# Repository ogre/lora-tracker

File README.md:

# SUSF LoRa HAB Tracker System 

Phil currently uses the following combination:

### *slim-board/* - Eagle layout of a slimline HAB Tracker PCB

* AAA Energizer Ultimate L92 Lithium power source
* ADP1607 DC-DC Boost Regulator
* STM32F030 Microcontroller
* u-blox MAX-M8x GNSS Receiver
* RFM98W 434MHz LoRa Transceiver Module

### *firmware-tracker-phil/* - Firmware for LoRa/RTTY HAB Trackers

* libopencm3-based firmware
* payload-switched config system
* u-blox GNSS aid data storage

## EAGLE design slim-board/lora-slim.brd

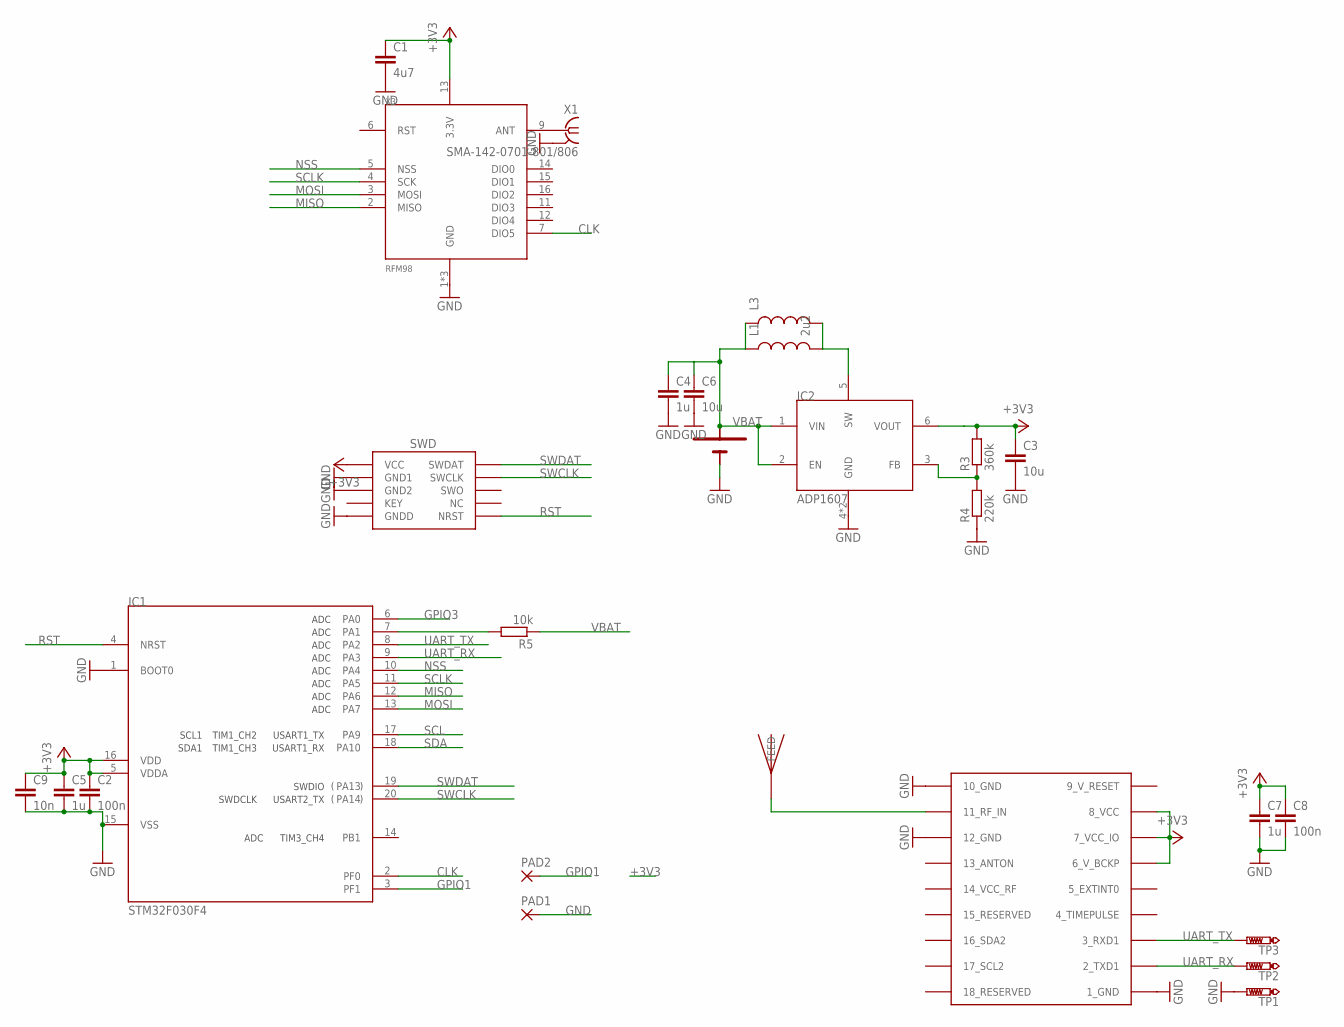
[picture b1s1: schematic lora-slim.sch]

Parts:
C1: 4u7; C0603
C2, C8: 100n; C0603
C3, C6: 10u; C0805
C4, C5, C7: 1u; C0603
C9: 10n; C0603
IC1: STM32F030F4; TSSOP20
IC2: ADP1607; LFCSP6
J1: SWD_PTH_SHROUD
L1: 2u2; 0805
L3: INDUCTOR1210; 1210
PAD1, PAD2: 2,15/1,0
R3: 360k; R0603
R4: 220k; R0603
R5: 10k; R0603
TP1, TP2, TP3: PTR1B1,27; B1,27
U$5: JTI_ANTENNA-1575AT43A40
U$6: KEYSTONE-53; KEYSTONE53
X1: SMA-142-0701-801/806; J502-ND-142-0701-801/806
X2: UBLOX_MAX
X3: RFM98; RFM97

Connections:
9_V_RESET: X2.9_V_RESET
+3V3: C1.1, C2.1, C3.1, C5.1, C7.1, C8.1, C9.1, IC1.5 (VDDA), IC1.16 (VDD), IC2.6 (VOUT), J1.1 (VCC), R3.2, X2.6_V_BCKP, X2.7_VCC_IO, X2.8_VCC, X3.13 (3.3V)
CLK: IC1.2 (PF0), X3.7 (DIO5)
GND: C1.2, C2.2, C3.2, C4.2, C5.2, C6.2, C7.2, C8.2, C9.2, IC1.1 (BOOT0), IC1.15 (VSS), IC2.4 (GND), IC2.EP (GND), J1.3 (GND1), J1.5 (GND2), J1.9 (GNDD), PAD1.1, R4.1, TP1.TP, U$6.N1 (-), U$6.N2 (-), X1.G@1 (2), X1.G@2 (2), X1.G@3 (2), X1.G@4 (2), X2.1_GND, X2.10_GND, X2.12_GND, X3.1 (GND), X3.8 (GND), X3.10 (GND)
GPIO1: IC1.3 (PF1), PAD2.1
GPIO3: IC1.6 (PA0)
MISO: IC1.12 (PA6), X3.2 (MISO)
MOSI: IC1.13 (PA7), X3.3 (MOSI)
unnamed: U$5.FEED, X2.11_RF_IN
unnamed: X1.1, X3.9 (ANT)
unnamed: IC2.5 (SW), L1.2, L3.2
unnamed: IC2.3 (FB), R3.1, R4.2
unnamed: IC1.7 (PA1), R5.2
NSS: IC1.10 (PA4), X3.5 (NSS)
RST: IC1.4 (NRST), J1.10 (NRST)
SCL: IC1.17 (PA9)
SCLK: IC1.11 (PA5), X3.4 (SCK)
SDA: IC1.18 (PA10)
SWCLK: IC1.20 (PA14), J1.4 (SWCLK)
SWDAT: IC1.19 (PA13), J1.2 (SWDAT)
UART_RX: IC1.9 (PA3), TP2.TP, X2.2_TXD1
UART_TX: IC1.8 (PA2), TP3.TP, X2.3_RXD1
VBAT: C4.1, C6.1, IC2.1 (VIN), IC2.2 (EN), L1.1, L3.1, R5.1, U$6.P1 (+), U$6.P2 (+)

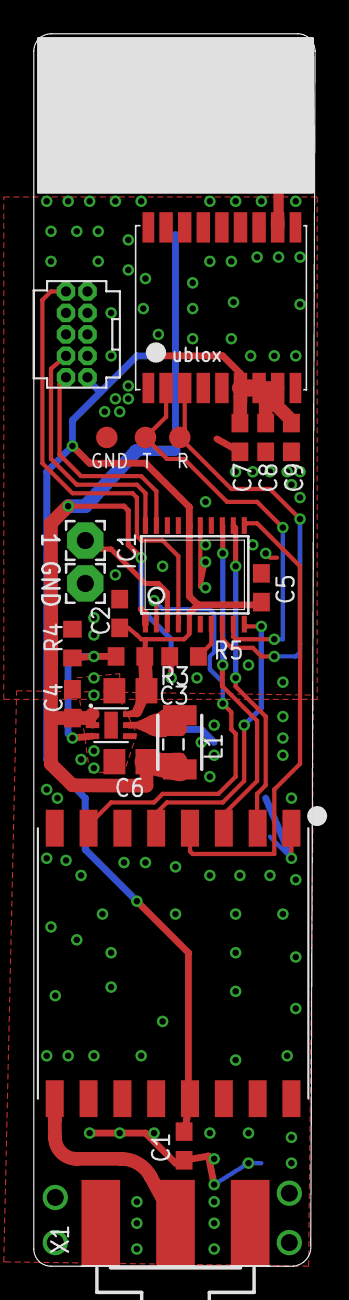
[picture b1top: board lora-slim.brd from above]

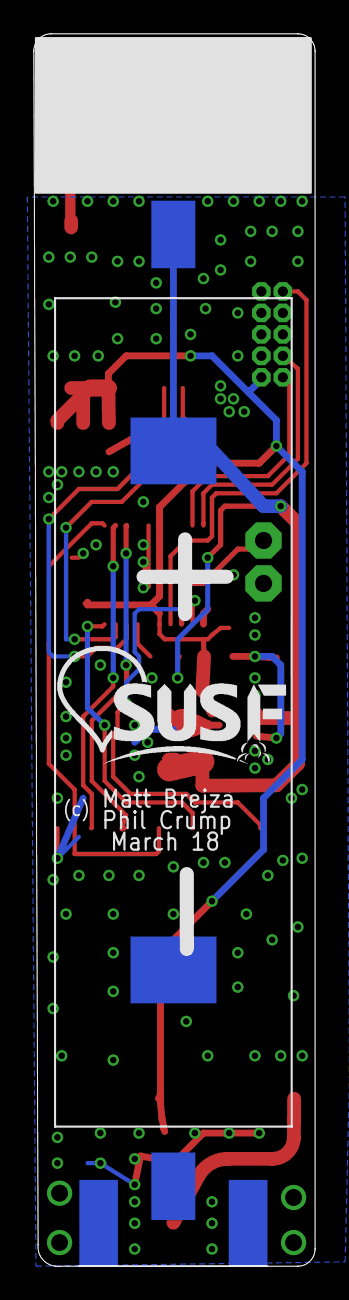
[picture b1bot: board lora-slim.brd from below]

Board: 2 copper layers, 16.6 x 72.9 mm, 28 parts (2 on the bottom side), 19 nets.

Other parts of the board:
U$1: SUSF-XSM

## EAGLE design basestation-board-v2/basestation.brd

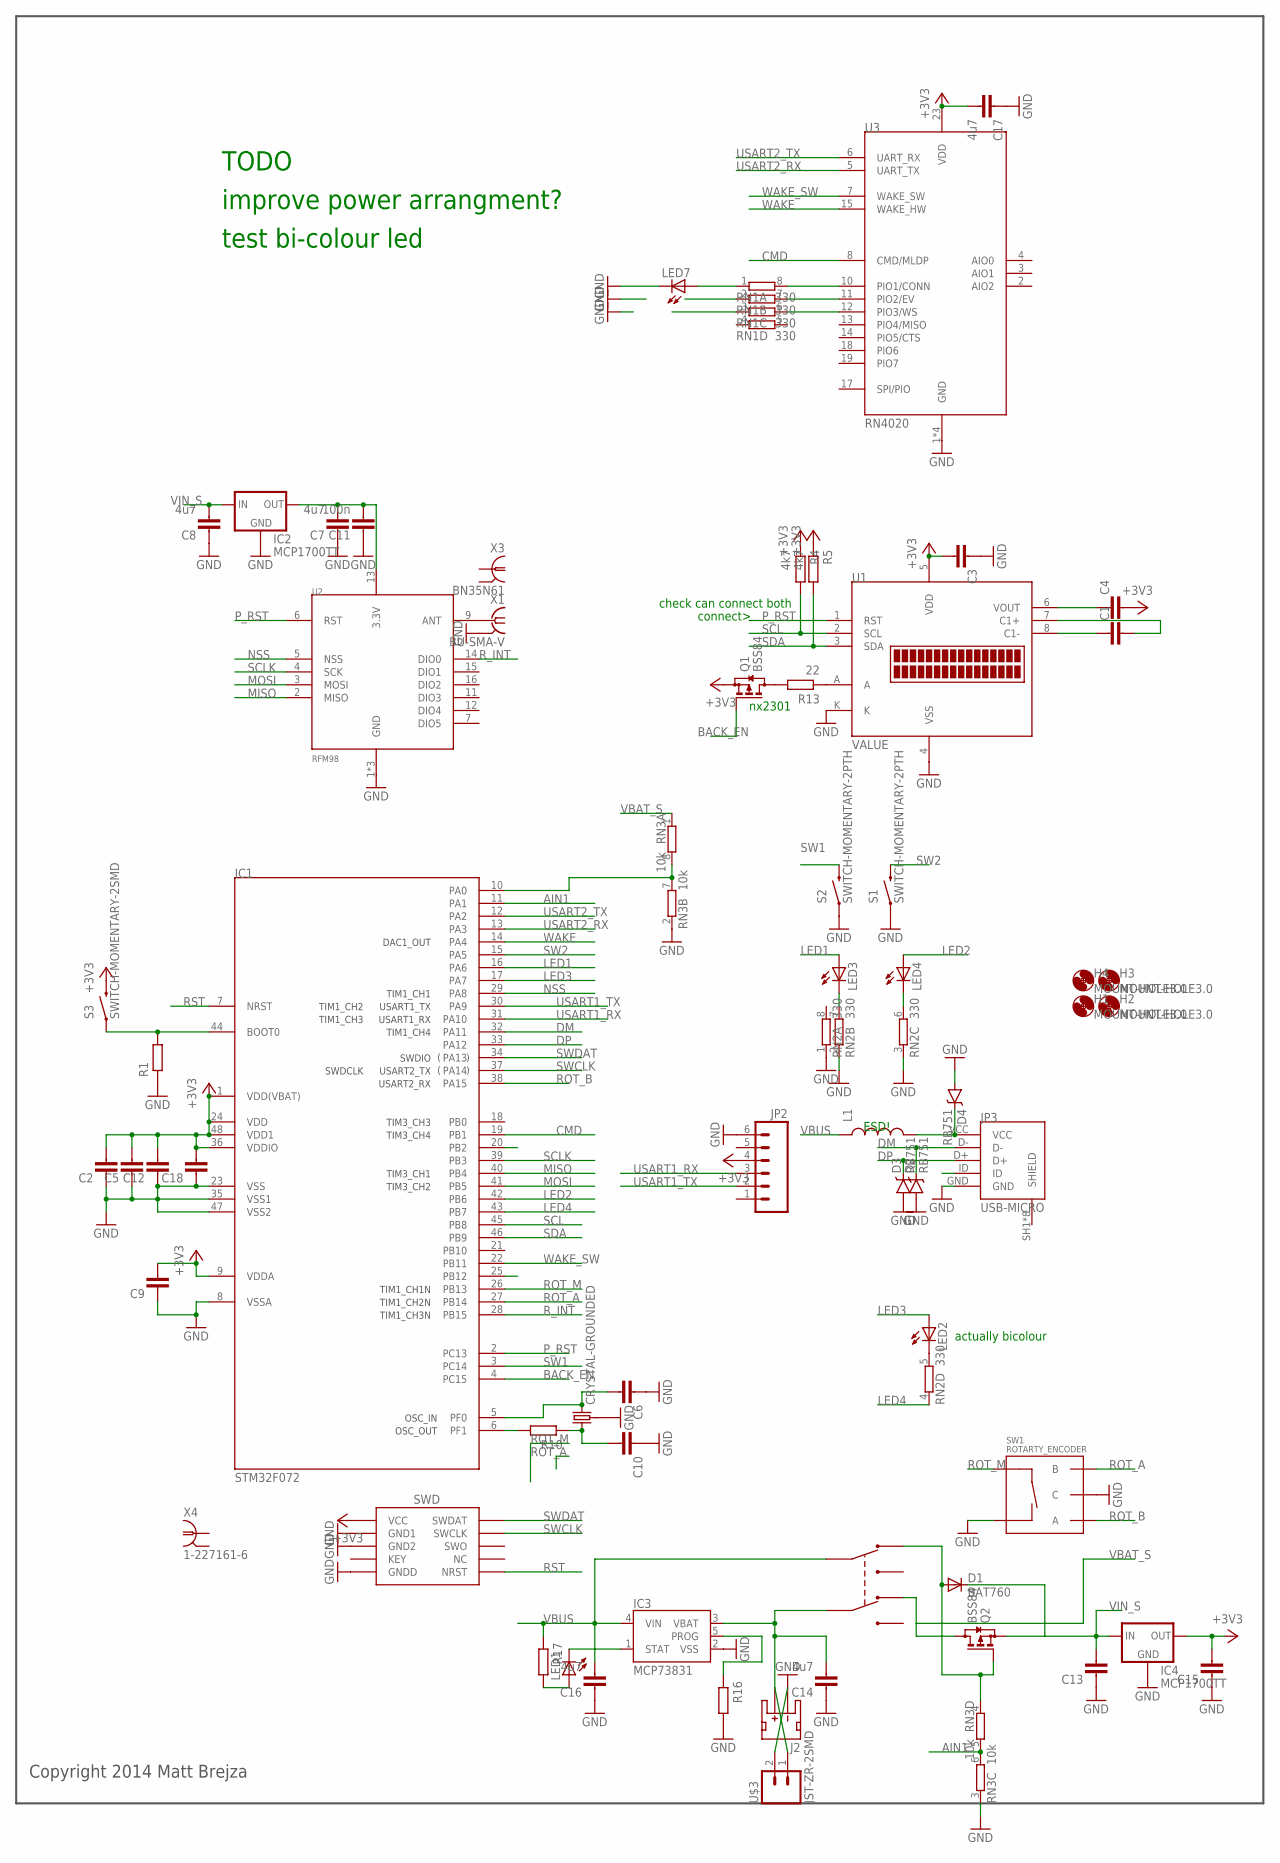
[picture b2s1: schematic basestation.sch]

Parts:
C1, C2, C3, C4, C5, C6, C9, C10, C12, C13, C15, C18: CAPACITOR0603-N; C0603-N
C7, C8, C14, C16, C17: 4u7; C0603-N
C11: 100n; C0603-N
D1: BAT760; SOD323-R
D2, D3, D4: RB751; SOD-523
H1, H2, H3, H4: MOUNT-HOLE3.0; 3,0
IC1: STM32F072; TQFP48
IC2, IC4: MCP1700TT; SOT23
IC3: MCP73831; SOT23-5
J1: SWD_SHROUD_SMD; SWD_SMD_SHROUD
J2: JST_2MM_MALE; JST-2-SMD
JP2: M06SMD; 1X06-SMD
JP3: USB-MICRO; MOLEX_47589-0001
L1: INDUCTOR0603; 0603
LED1, LED7: LEDCHIP-LED0805; CHIP-LED0805
LED2: LED5MM
LED3, LED4: LED3MM
Q1, Q2: BSS84; SOT23
R1, R10, R16, R17: RESISTOR0603-N; R0603-N
R4, R5: 4k7; R0603-N
R13: 22; R0603-N
RN1, RN2: 330; EXB38V
RN3: 10k; EXB38V
S1, S2: SWITCH-MOMENTARY-2PTH; TACTILE-PTH
S3: SWITCH-MOMENTARY-2SMD; TACTILE_SWITCH_SMD
SW1: ROTARTY_ENCODER; ROTARY_ENC_PLAIN
U1: NHD-C0216CIZ-FSW
U2: RFM98; RFM97
U3: RN4020
U$1: DPDTSLIDE
U$3: JST-ZR-2SMD; JST-ZR-2-SMD
X1: BU-SMA-V
X2: CRYSTAL-GROUNDED; CRYSTAL-SMD-5X3
X3: BN35N61; B35N61
X4: 1-227161-6; AMP_227161

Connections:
3.3V: C7.2, C11.2, IC2.2 (OUT), U2.13 (3.3V)
+3V3: C2.2, C3.2, C4.2, C5.2, C9.2, C12.2, C15.2, C17.2, C18.2, IC1.1 (VDD(VBAT)), IC1.9 (VDDA), IC1.24 (VDD), IC1.36 (VDDIO), IC1.48 (VDD1), IC4.2 (OUT), J1.1 (VCC), JP2.4, Q1.2 (S), R4.1, R5.1, S3.3 (2), U1.5 (VDD), U3.23 (VDD)
AIN1: IC1.11 (PA1), RN3.5 (2), RN3.6 (2)
BACK_EN: IC1.4 (PC15), Q1.1 (G)
CMD: IC1.19 (PB1), U3.8 (CMD/MLDP)
DM: D2.C, IC1.32 (PA11), JP3.D-
DP: D3.C, IC1.33 (PA12), JP3.D+
GND: C2.1, C3.1, C5.1, C6.1, C7.1, C8.1, C9.1, C10.1, C11.1, C12.1, C13.1, C14.1, C15.1, C16.1, C17.1, C18.1, D2.A, D3.A, D4.A, IC1.8 (VSSA), IC1.23 (VSS), IC1.35 (VSS1), IC1.47 (VSS2), IC2.1 (GND), IC3.2 (VSS), IC4.1 (GND), J1.3 (GND1), J1.5 (GND2), J1.9 (GNDD), J2.1 (-), JP2.6, JP3.GND, LED7.C, R1.1, R16.2, RN2.1, RN2.2 (1), RN2.3 (1), RN3.2 (1), RN3.3 (1), S1.1, S2.1, SW1.C, SW1.SW-, U1.4 (VSS), U1.K, U2.1 (GND), U2.8 (GND), U2.10 (GND), U3.1 (GND), U3.9 (GND), U3.16 (GND), U3.24 (GND), U$3.2, X1.2, X1.3 (2), X1.4 (2), X1.5 (2), X2.2 (3), X2.4 (3)
LED1: IC1.16 (PA6), LED3.A
LED2: IC1.42 (PB6), LED4.A
LED3: IC1.17 (PA7), LED2.A
LED4: IC1.43 (PB7), RN2.4 (1)
MISO: IC1.40 (PB4), U2.2 (MISO)
MOSI: IC1.41 (PB5), U2.3 (MOSI)
unnamed: U2.9 (ANT), X1.1
unnamed: Q1.3 (D), R13.2
unnamed: IC1.44 (BOOT0), R1.2, S3.1
unnamed: RN1.8 (2), U3.10 (PIO1/CONN)
unnamed: LED3.K (C), RN2.7 (2)
unnamed: IC3.5 (PROG), R16.1
unnamed: C1.1, U1.8 (C1-)
unnamed: C1.2, U1.7 (C1+)
unnamed: LED4.K (C), RN2.6 (2)
unnamed: LED2.K (C), RN2.5 (2)
unnamed: C4.1, U1.6 (VOUT)
unnamed: RN1.7 (2), U3.11 (PIO2/EV)
unnamed: RN1.6 (2), U3.12 (PIO3/WS)
unnamed: LED7.A, RN1.1
unnamed: R13.1, U1.A
unnamed: D1.A, Q2.1 (G), RN3.4 (1), U$1.1A (NC0)
unnamed: IC1.10 (PA0), RN3.7 (2), RN3.8 (2)
unnamed: IC3.1 (STAT), LED1.C
unnamed: IC1.6 (PF1), R10.2
unnamed: C6.2, IC1.5 (PF0), X2.1 (2)
unnamed: C10.2, R10.1, X2.3 (1)
unnamed: C14.2, IC3.3 (VBAT), J2.2 (+), U$1.2X (COM1), U$3.1
unnamed: LED1.A, R17.2
unnamed: D4.C, JP3.VCC, L1.2
NSS: IC1.29 (PA8), U2.5 (NSS)
P_RST: IC1.2 (PC13), U1.1 (RST), U2.6 (RST)
ROT_A: IC1.27 (PB14), SW1.B
ROT_B: IC1.38 (PA15), SW1.A
ROT_M: IC1.26 (PB13), SW1.SW+
RST: IC1.7 (NRST), J1.10 (NRST)
R_INT: IC1.28 (PB15), U2.14 (DIO0)
SCL: IC1.45 (PB8), R4.2, U1.2 (SCL)
SCLK: IC1.39 (PB3), U2.4 (SCK)
SDA: IC1.46 (PB9), R5.2, U1.3 (SDA)
SW1: IC1.3 (PC14), S2.3 (2)
SW2: IC1.15 (PA5), S1.3 (2)
SWCLK: IC1.37 (PA14), J1.4 (SWCLK)
SWDAT: IC1.34 (PA13), J1.2 (SWDAT)
USART1_RX: IC1.31 (PA10), JP2.3
USART1_TX: IC1.30 (PA9), JP2.2
USART2_RX: IC1.13 (PA3), U3.5 (UART_TX)
USART2_TX: IC1.12 (PA2), U3.6 (UART_RX)
VBAT_S: Q2.3 (D), RN3.1, U$1.2A (NC1)
VBUS: C16.2, IC3.4 (VIN), L1.1, R17.1, U$1.1X (COM0)
VIN_S: C8.2, C13.2, D1.C, IC2.3 (IN), IC4.3 (IN), Q2.2 (S)
WAKE: IC1.14 (PA4), U3.15 (WAKE_HW)
WAKE_SW: IC1.22 (PB11), U3.7 (WAKE_SW)

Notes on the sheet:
actually bicolour
connect>
nx2301
ESD!
check can connect both
Copyright 2014 Matt Brejza
TODO
improve power arrangment?
test bi-colour led

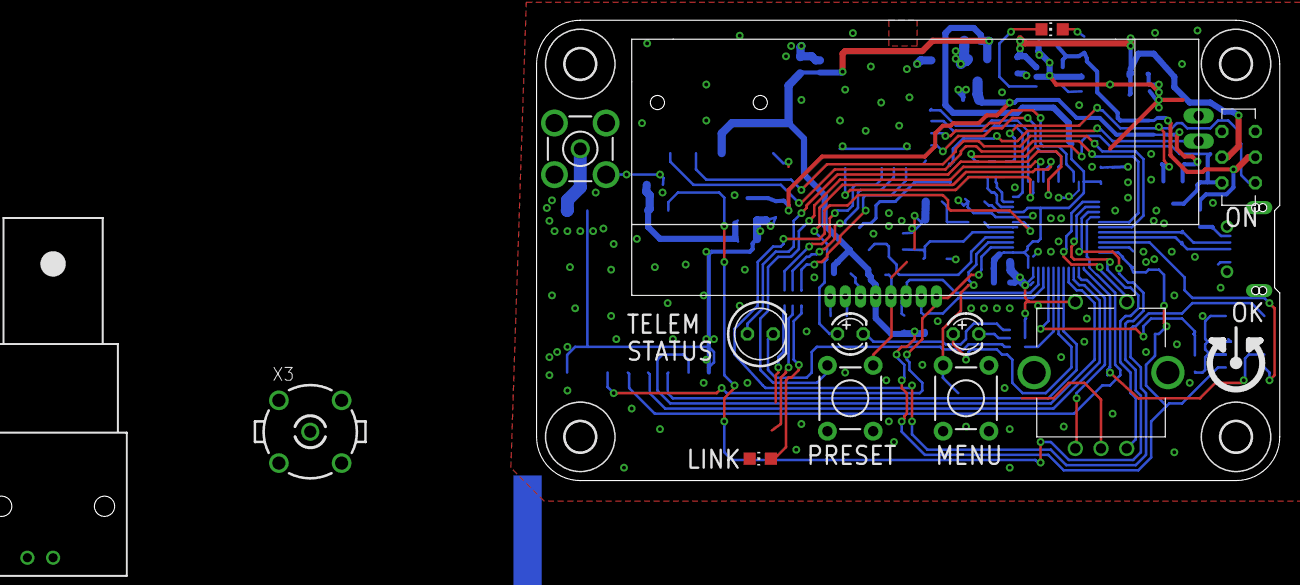
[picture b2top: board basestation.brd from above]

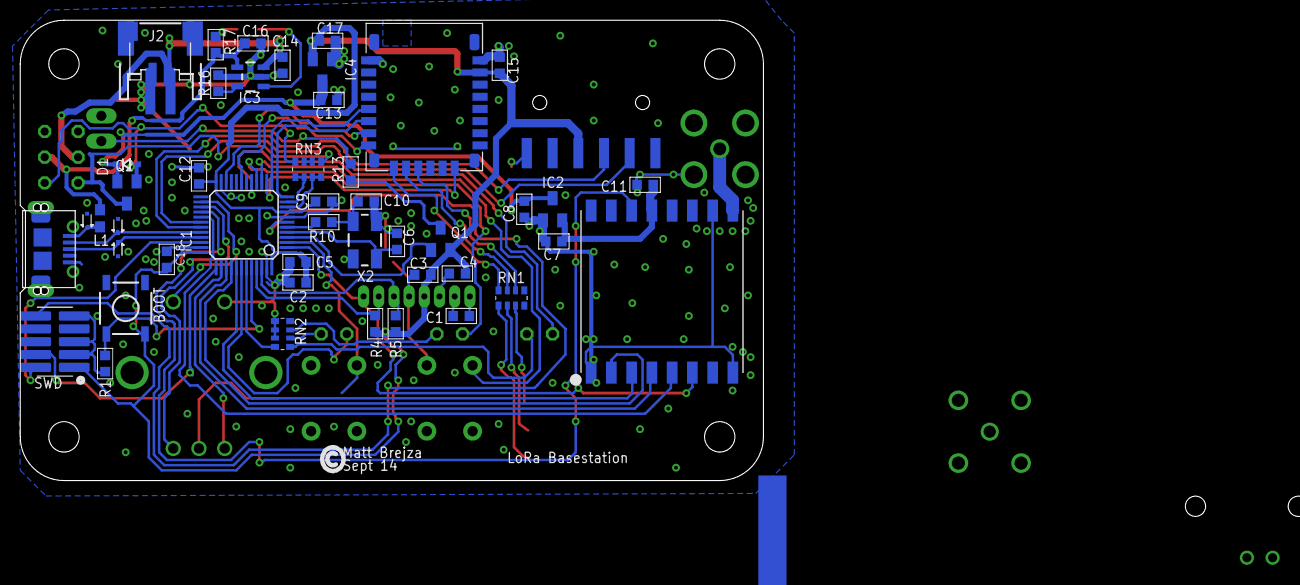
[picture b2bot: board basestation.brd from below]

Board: 2 copper layers, 73.4 x 45.5 mm, 65 parts (48 on the bottom side), 61 nets.

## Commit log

2015-05-10 initial commir of v2 board
2016-01-17 improvments
2018-03-16 firmware-tracker: Add .d & .map to gitignore.
2018-03-16 firmware-tracker: Patch Makefiles for my environment.
2018-03-16 firmware-tracker: Remove old files, copy in cmp & liblora(radio) files.
2018-03-16 firmware-tracker/main.c: Add flag to select ublox message version.
2018-03-16 firmware-tracker/main.c: Use gnss_status_updated to detect gps activity, fixing disabling gps.
2018-03-16 firmware-tracker/main.c: Changes for CRAAG4.
2018-03-16 firmware-tracker: Fix compile warnings
2018-03-16 firmware-tracker/main.c: Add timeout to new gps info wait, reconfigure gps if timeout triggered.
2018-03-16 firmware-tracker: Break payload config out to payload_config.h
2018-03-17 firmware-tracker: Update libopencm3.
2018-04-01 Update slim-lora board. [inverted battery, remove gps rf parts, rework reg layout, add gpio1 header]
2018-04-02 Tracker firmware improvements WIP.
2018-04-02 Update locm3.
2018-04-26 slim-board: Tweak cap values.
2018-04-26 Fork phil tracker code.
2018-04-29 Habpack firmware tweaks.
2018-04-29 firmware-tracker-phil tweaks.
2018-04-29 Add Calling Beacon on 433.650
2018-05-06 Update libopencm3.
2018-05-06 Revert "Update libopencm3."
    This reverts commit 69e38a9cdd66d5bdd3547cc0053f84e7e362a363.
2018-05-06 phil-tracker-firmware: Updates, RTF?
2018-05-06 Use float for rtty.
2018-05-06 Add NAV5 polling seq (unused).
2018-05-06 flash: Add rudimentary flash/ram sizing report.
2018-05-07 Add download of gps+glo almanac into flash.
2018-05-07 Break out gnss variables into payload configs.
2018-05-14 Minor tooling tweaks.
2018-05-14 Application tweaks for less stack usage.
2018-05-14 Clean up unused files.
2018-05-14 Small tweaks.
2018-05-22 Expand GNSS Aid Data (limited by rom size).
2018-05-22 handle lack of authtoken.
2018-05-22 Add build-only script and first CI attempt.
2018-05-22 Fix locm3 submodule.
2018-05-22 Fix lack of authtoken.
2018-05-22 Update for latest libopencm3 (untested).
2018-05-22 Add blank gnss_aid template to git.
2018-06-26 configs: Use sizeof(const) rather than hardcoded length.
2018-06-26 Add EGNOS SBAS Configuration.
2018-06-26 Update locm3 ref.
2018-07-01 firmware-tracker: Calc ubx checksums to save space, parameterise pos gnss aid.
2018-07-01 firmware-tracker: Print GNSS aid summary at compile.
2018-07-01 firmware-tracker: Flash fixes.
2018-07-01 firmware-tracker: Remove redundant data printout.
2018-07-08 Fix GNSS blank template for no gnss data.
2018-07-08 Force interpretation of DoM as base-10.
2018-07-08 Configs: Update for GES position.
2018-08-13 firmware-phil/gnss_aid: Fix parsing of curl errors return code.
2018-08-13 firmware-phil/gnss_aid: Ignore cached GNSS Aid data if too old.
2018-08-13 firmware-phil/gnss_aid/blank_template: Disable Aid functions that we cant do with blank template.
2018-09-24 .travis.yml: Update gcc link.
2018-12-08 Add README.md

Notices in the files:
parts and their libraries:
SparkFun-Electromechanical: Licensing: Creative Commons ShareAlike 4.0 International - https://creativecommons.org/licenses/by-sa/4.0
SparkFun-DiscreteSemi: Licensing: CC v3.0 Share-Alike You are welcome to use this library for commercial purposes.
